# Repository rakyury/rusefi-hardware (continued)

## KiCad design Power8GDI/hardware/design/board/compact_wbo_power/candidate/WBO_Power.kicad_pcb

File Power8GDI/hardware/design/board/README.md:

# Review PCB builder

**Incomplete engineering PCB. Do not fabricate, energize or claim qualification.**
The original placeholder PCB is untouched. This folder builds real footprints,
pad nets and routed subdomains from the current electrical hierarchy.

Use the pinned official `kicad/kicad:9.0` image, KiCad9.0.9; digest is recorded
in `source_provenance.json`. No network is needed during generation. Mount the
repository at`/src`, set working directory`/src`, and run:

```text
python3 Power8GDI/hardware/design/board/build_connector_schematic.py
kicad-cli sch export netlist --format kicadxml -o Power8GDI/hardware/design/board/connectors.xml Power8GDI/hardware/design/board/connectors.kicad_sch
python3 Power8GDI/hardware/design/board/build_board.py
python3 Power8GDI/hardware/design/board/verify_board.py Power8GDI/hardware/design/board/review/Power8GDI_Review.kicad_pcb Power8GDI/hardware/design/core.net
kicad-cli pcb drc --format json --all-track-errors --severity-all --exit-code-violations -o Power8GDI/hardware/design/board/review/drc.json Power8GDI/hardware/design/board/review/Power8GDI_Review.kicad_pcb
```

The authoritative integrated root XML is `design/core.net`. It includes
J601..604, so the current verifier uses only this XML. Duplicate refs
and conflicting pad assignments are errors. Before root integration the
builder also accepts whole separate GDI/power XML sheets; a partially duplicate
hierarchy is rejected. `--design-root`, `--source-board`, `--pinout` and
`--output-dir` support isolated build snapshots without editing source designs.

Source electrical flags includingDNP and BOM exclusion are carried to the
physical board and independently compared on reload. A source off-board
component fails instead of silently becoming a physical pad.

The copper transfer uses KiCad's actual source connectivity graph, exact
oldref→newref mapping and sourcepad→targetnet mapping. It rejects any source
net that would join two distinct target nets. Branches terminating at removed
logic/connectors and open physical endpoints are removed. Ground vias count
as real plane endpoints only with a retained pad. Groundplane fill and DRC are
run on the resulting board. Reference power/sense-zone shapes remain visible;
source clearances are **not** automatically accepted as new design rules.

The stageB reference3V3/5V supply buses cross the provisional edge when rotated;
they are explicitly omitted for rerouting to the new regulators. Remaining
unrouted connections are reported, not represented by invented tracks.

The provisional outline245×165mm,4-layer1.6mm stackup and clearances are design
inputs, not a manufacturer's approved stackup. Outer copper70µm, inner35µm,
dielectrics120/1130/120µm, soldermask10µm each side are an engineering proposal.
Current, thermal, impedance, transient, dielectric and assembly budgets remain
open. PCB pads/trace exports alone do not demonstrate electrical qualification.

The outline, donor stage frames, connector/MCU/ignition anchors and functional
regions come from `layout_profiles/<name>.json` (`--layout-profile`, default
`layout_profiles/245x165.json`). `compare_boards.py A B` proves two builds are
geometrically identical. See `docs/PCB_LAYOUT_PROFILE_2026_11_05.md`.

Run portable contract tests with:

```text
python -m unittest discover -s Power8GDI/hardware/design/board/tests -v
```

`render_preview.py` optionally converts actual KiCad SVG plots toPNG using
PyQt6/QtSvg. It does not infer or invent copper. Rendered exports and full DRC
reports belong in the chosen build/output directory; no manufacturing Gerber
release is produced while the DRC and functional gates fail.

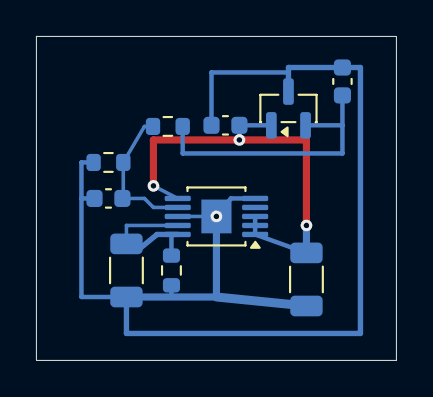
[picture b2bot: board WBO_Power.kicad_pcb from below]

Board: 4 copper layers, 20.0 x 18.0 mm, 10 parts (10 on the bottom side), 5 nets.

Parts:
C5617: 100n; C_0603_1608Metric
C5660, C5664: 100n 16V X7R; C_0603_1608Metric
C5661, C5662: 10u 16V X7R effective>=4.7u; C_1206_3216Metric
R5660: 30k 0.1%; R_0603_1608Metric
R5661: 2.2k 1%; R_0603_1608Metric
R5663: 220R 0.1%; R_0603_1608Metric
U5603: REF3033AIDBZR; SOT-23
U5604: LT3042IMSE#WTRPBF; MSOP-10-1EP_3x3mm_P0.5mm_EP1.68x1.88mm

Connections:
+5V_CORE: C5617.1, C5661.1, U5603.1, U5604.1, U5604.2, U5604.3, U5604.6
GND: C5617.2, C5660.2, C5661.2, C5662.2, C5664.2, R5660.2, R5661.2, U5603.3, U5604.5, U5604.8, U5604.11
WBO1_3V3: C5662.1, R5661.1, U5604.9, U5604.10
WBO1_REF3V3: C5664.1, R5663.1, U5603.2
WBO1_REF_SET: C5660.1, R5660.1, R5663.2, U5604.7

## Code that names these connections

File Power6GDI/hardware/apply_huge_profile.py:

"""Apply the reviewed GDI8/four-motor resource revision without guessing pins."""
import csv
import json
from pathlib import Path

HERE=Path(__file__).resolve().parent
ROOT=HERE.parent

def main():
    path=HERE/'mcu_gpio_draft.csv'
    rows=list(csv.DictReader(path.open(encoding='utf-8-sig')))
    removed={'DIN5','DIN6','DIN7','DIN8','WBO1_CS_N','WBO2_CS_N','WBO_ADC_CS_N'}
    rows=[r for r in rows if r['function'] not in removed]
    revised={
      'HPFP1':('PD8','GPIO_TIMED','Dedicated scheduled pump command; moved offPC9 to reserve TIM3_CH4'),
      'DBW_DIR':('PI2','GPIO','Direction GPIO moved offPC7 to reserve TIM3_CH2'),
      'MOTOR3_PWM':('PC7','TIM3_CH2','DS11532 Table11 p78/AF2; same PWM frequency as other motor bridges'),
      'MOTOR3_DIR':('PI3','GPIO','Reserve motor direction; default low'),
      'MOTOR3_DISABLE':('PI10','GPIO','Reserve motor disable; external default high'),
      'MOTOR4_PWM':('PC9','TIM3_CH4','DS11532 Table11 p78/AF2; same PWM frequency as other motor bridges'),
      'MOTOR4_DIR':('PI4','GPIO','Reserve motor direction; default low'),
      'MOTOR4_DISABLE':('PI11','GPIO','Reserve motor disable; external default high'),
      'MOTOR_CS_N':('PB4','GPIO','Four TLE9201 diagnostics daisy-chain CS; external pullup and isolated MISO'),
      'WBO1_HEATER_PWM':('PA10','GPIO','Main-MCU heater permission, default low; local F042 supplies actual PWM'),
      'WBO2_HEATER_PWM':('PB2','GPIO','Main-MCU heater permission, default low; local F042 supplies actual PWM'),
    }
    by_name={r['function']:r for r in rows}
    for name,(pin,mode,note) in revised.items():
        row={'function':name,'stm32_pin':pin,'mcu_resource':mode,'status':'proposed','notes':note}
        if name in by_name:by_name[name].update(row)
        else:rows.append(row)
    pins=[r['stm32_pin'] for r in rows if r['stm32_pin']!='UNASSIGNED']
    assert len(pins)==len(set(pins)), 'Pin collision in explicit scope migration'
    with path.open('w',encoding='utf-8',newline='') as f:
        writer=csv.DictWriter(f,fieldnames=['function','stm32_pin','mcu_resource','status','notes'])
        writer.writeheader();writer.writerows(rows)
    contract_path=HERE/'resource_contract.json'
    contract=json.loads(contract_path.read_text())
    contract['named_requirements']=[n for n in contract['named_requirements'] if n not in removed]
    for name in revised:
        if name not in contract['named_requirements'] and name!='HPFP1':contract['named_requirements'].append(name)
    contract['decisions']['motor_pwm_timebase']='TIM3_CH1_to_CH4_shared_frequency'
    # Old source observations are retained, but withdrawn functions are no longer active allocations.
    for group,items in list(contract['candidate_pin_evidence'].items()):
        if isinstance(items,dict):
            for name in removed:items.pop(name,None)
        elif isinstance(items,list):
            contract['candidate_pin_evidence'][group]=[x for x in items if not isinstance(x,dict) or x.get('function') not in removed]
    contract['candidate_pin_evidence']['four_motor_revision']={
        name:{'port':pin,'mode':mode,'note':note} for name,(pin,mode,note) in revised.items()}
    contract['sources']['DS11532']['locators'].append('Table11 p78 and Table13 PortC: PC6..PC9 AF2 TIM3_CH1..4') if 'Table11 p78 and Table13 PortC: PC6..PC9 AF2 TIM3_CH1..4' not in contract['sources']['DS11532']['locators'] else None
    contract_path.write_text(json.dumps(contract,indent=2)+'\n')
    path=ROOT/'pinout/power8gdi_revA_pinout.csv'
    rows=list(csv.DictReader(path.open(encoding='utf-8-sig')))
    for row in rows:
        if row['net'] in {'DIN5','DIN6','DIN7','DIN8'}:
            row['net']={'DIN5':'MOTOR3_MOTOR_A','DIN6':'MOTOR3_MOTOR_B','DIN7':'MOTOR4_MOTOR_A','DIN8':'MOTOR4_MOTOR_B'}[row['net']]
            row['group']='H-Bridge' if 'group' in row else row.get('group','')
            # Preserve the actual source CSV schema (some revisions use category).
            if 'category' in row:row['category']='H-Bridge'
            row['notes']='Reserved H-bridge motor terminal; previous DIN allocation superseded2026-10-23'
        if row['net'].startswith('IGN'):
            row['notes']='Passive B58 coil primary low-side; logic-coil assembly alternative must be mutually exclusive'
    fields=list(csv.DictReader(path.open(encoding='utf-8-sig')).fieldnames)
    with path.open('w',encoding='utf-8',newline='') as f:
        writer=csv.DictWriter(f,fieldnames=fields,extrasaction='ignore');writer.writeheader();writer.writerows(rows)
    print(f'Applied Huge GDI8 profile: {len(pins)} unique GPIO allocations; 4 motor terminal pairs')

if __name__=='__main__':main()

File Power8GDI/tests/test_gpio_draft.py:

"""Static constraints only: AF, DMA, connector/current checks not complete."""
import csv
from pathlib import Path
import unittest

ROOT = Path(__file__).resolve().parents[1]


class GpioDraftContract(unittest.TestCase):
    @classmethod
    def setUpClass(cls):
        with (ROOT / 'hardware/mcu_gpio_draft.csv').open(newline='') as f:
            cls.data = list(csv.DictReader(f))
        cls.pins = {item['function']: item['stm32_pin'] for item in cls.data}

    def test_names_unique(self):
        self.assertEqual(len(self.pins), len(self.data))

    def test_assigned_pins_have_no_collision(self):
        assigned = [row['stm32_pin'] for row in self.data if row['stm32_pin'] != 'UNASSIGNED']
        self.assertEqual(len(assigned), len(set(assigned)))

    def test_gdi_resources(self):
        for prefix, n in [('DI', 6), ('IGN', 6), ('HPFP', 2)]:
            for i in range(1, n + 1):
                self.assertNotEqual('UNASSIGNED', self.pins[f'{prefix}{i}'])
        for prefix in ('PTA', 'PTB'):
            for suffix in ('CS', 'RESET', 'DRVEN', 'FLAG'):
                self.assertNotEqual('UNASSIGNED', self.pins[f'{prefix}_{suffix}'])

    def test_two_distinct_motor_bridges(self):
        for prefix in ('DBW', 'EWG'):
            for suffix in ('PWM', 'DIR', 'DISABLE'):
                self.assertNotEqual('UNASSIGNED', self.pins[f'{prefix}_{suffix}'])

    def test_new_serial_routes_are_allocated(self):
        for signal,pin in {'LIN2_TX':'PB10','LIN2_RX':'PB11','CAN2_RX':'PB5','CAN2_TX':'PB6'}.items():
            self.assertEqual(pin, self.pins[signal])

    def test_new_receiver_assignments_remain_proposed(self):
        expected={'SENT3':'PE11','SENT4':'PB7','CAM3':'PI5','CAM4':'PI6'}
        for row in self.data:
            if row['function'] in expected:
                self.assertEqual(row['stm32_pin'],expected[row['function']])
                self.assertEqual(row['status'],'proposed')

    def test_requirements_dont_fit_only_four_tle9104(self):
        # Six PI + four VVT + eight general-purpose PWM + four service low-side.
        required_low_sides = 6 + 4 + 8 + 4
        self.assertEqual(required_low_sides, 22)
        self.assertGreater(required_low_sides, 4 * 4)
        self.assertEqual((required_low_sides + 3) // 4, 6)


if __name__ == '__main__':
    unittest.main()

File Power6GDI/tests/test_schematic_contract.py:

"""Active six-cylinder connector contract from the real KiCad XML export.

The old Power8GDI_RevA interface-only starter is historical, not a circuit.
"""
import csv
import re
import unittest
import xml.etree.ElementTree as ET
from pathlib import Path

ROOT = Path(__file__).resolve().parents[1]
SCHEMATIC = ROOT / "hardware/Power8GDI_RevA.kicad_sch"
PCB = ROOT / "hardware/Power8GDI_RevA.kicad_pcb"
NETLIST = ROOT / 'hardware/design/core.net'
PINOUT = ROOT / "pinout/power8gdi_revA_pinout.csv"


class SchematicContractTests(unittest.TestCase):
    @classmethod
    def setUpClass(cls):
        cls.doc = ET.parse(NETLIST)
        cls.pins = {(p.get('ref'),p.get('pin')):n.get('name') for n in cls.doc.findall('nets/net') for p in n.findall('node')}
        cls.aliases = {r['pinout_net']:r['board_net'] for r in csv.DictReader((ROOT/'hardware/design/board/connector_aliases.csv').read_text().splitlines())}
        with PINOUT.open(encoding="utf-8", newline="") as fp:
            cls.rows = list(csv.DictReader(fp))

    def test_csv_columns(self):
        self.assertEqual(
            ["connector", "pin", "position", "net", "group", "notes"],
            list(self.rows[0]),
        )

    def test_schematic_labels_exactly_match_pinout(self):
        self.assertEqual(len(self.rows),136)
        for row in self.rows:
            actual=self.pins[('J60'+str('ABCD'.index(row['connector'])+1),row['position'])]
            if row['net'].startswith('UNUSED_'): self.assertTrue(actual.startswith('unconnected-'))
            else: self.assertEqual(actual,self.aliases.get(row['net'],'HARNESS_'+row['net']))

    def test_four_interface_connectors(self):
        for ref in ['J601','J602','J603','J604']:
            self.assertEqual(len([p for r,p in self.pins if r==ref]),34)

    def test_all_cylinders_have_dedicated_injector_pairs(self):
        nets = [r['net'] for r in self.rows]
        for i in range(1, 7):
            self.assertEqual(nets.count(f'DI{i}_HIGH'),1)
            self.assertEqual(nets.count(f'DI{i}_LOW'),1)
        for prefix in ('DI7','DI8','PI7','PI8','IGN7','IGN8','MOTOR3','MOTOR4','WBO2'):
            self.assertFalse(any(n.startswith(prefix) for n in nets))

    def test_hpfp_pairs_are_separate(self):
        nets = {r["net"] for r in self.rows}
        self.assertTrue({"HPFP1_HIGH", "HPFP1_LOW", "HPFP2_HIGH", "HPFP2_LOW"} <= nets)

    def test_physical_removed_assemblies_do_not_reappear(self):
        refs={c.get('ref') for c in self.doc.findall('components/comp')}
        self.assertTrue({'U201','U301','U6000','U6050','U5602'} <= refs)
        self.assertFalse({'Q210','Q310','U6100','U6150','U5802','Q5540','Q5560','U5405'} & refs)


if __name__ == "__main__":
    unittest.main()
